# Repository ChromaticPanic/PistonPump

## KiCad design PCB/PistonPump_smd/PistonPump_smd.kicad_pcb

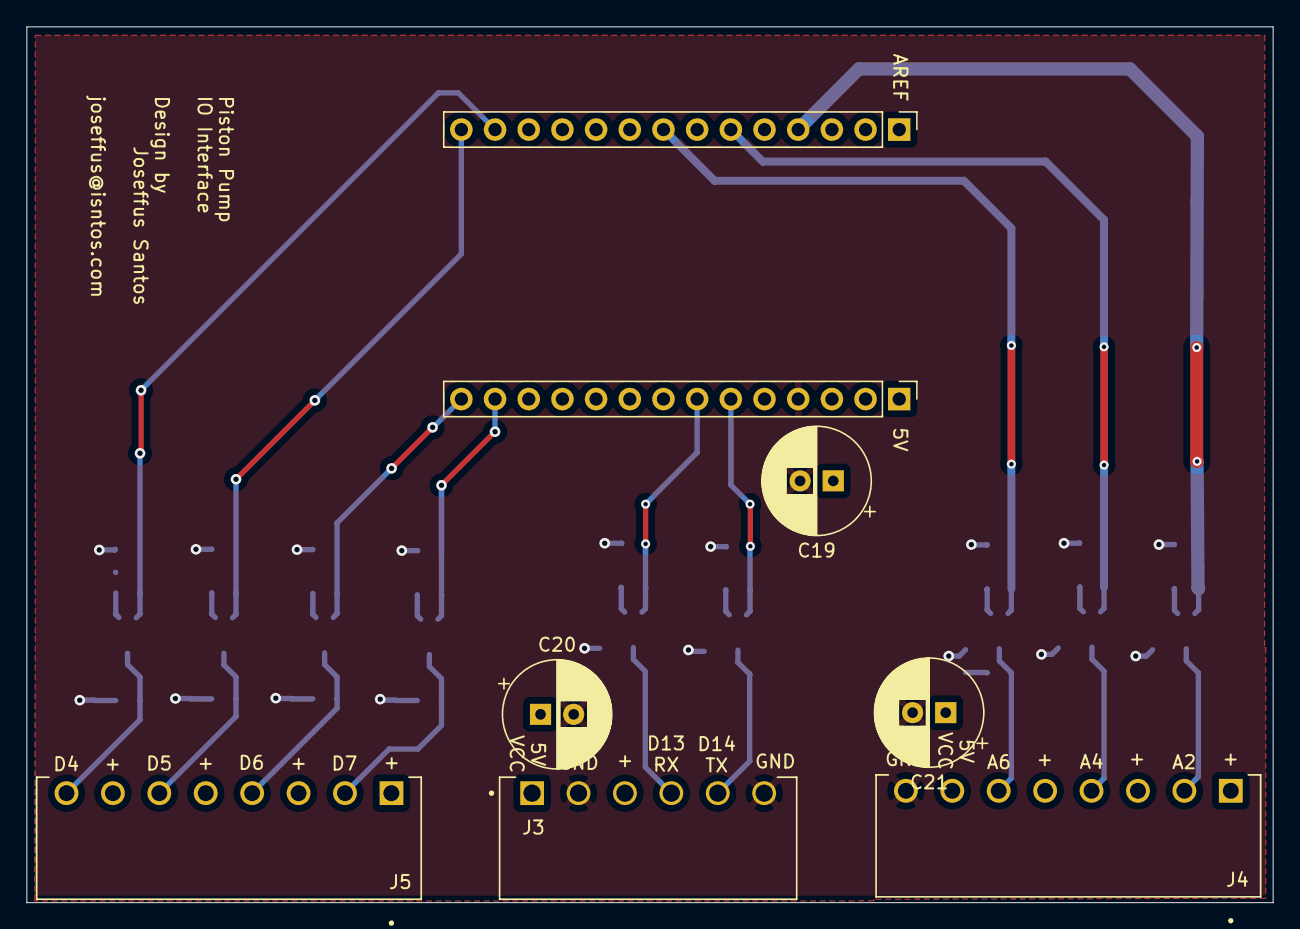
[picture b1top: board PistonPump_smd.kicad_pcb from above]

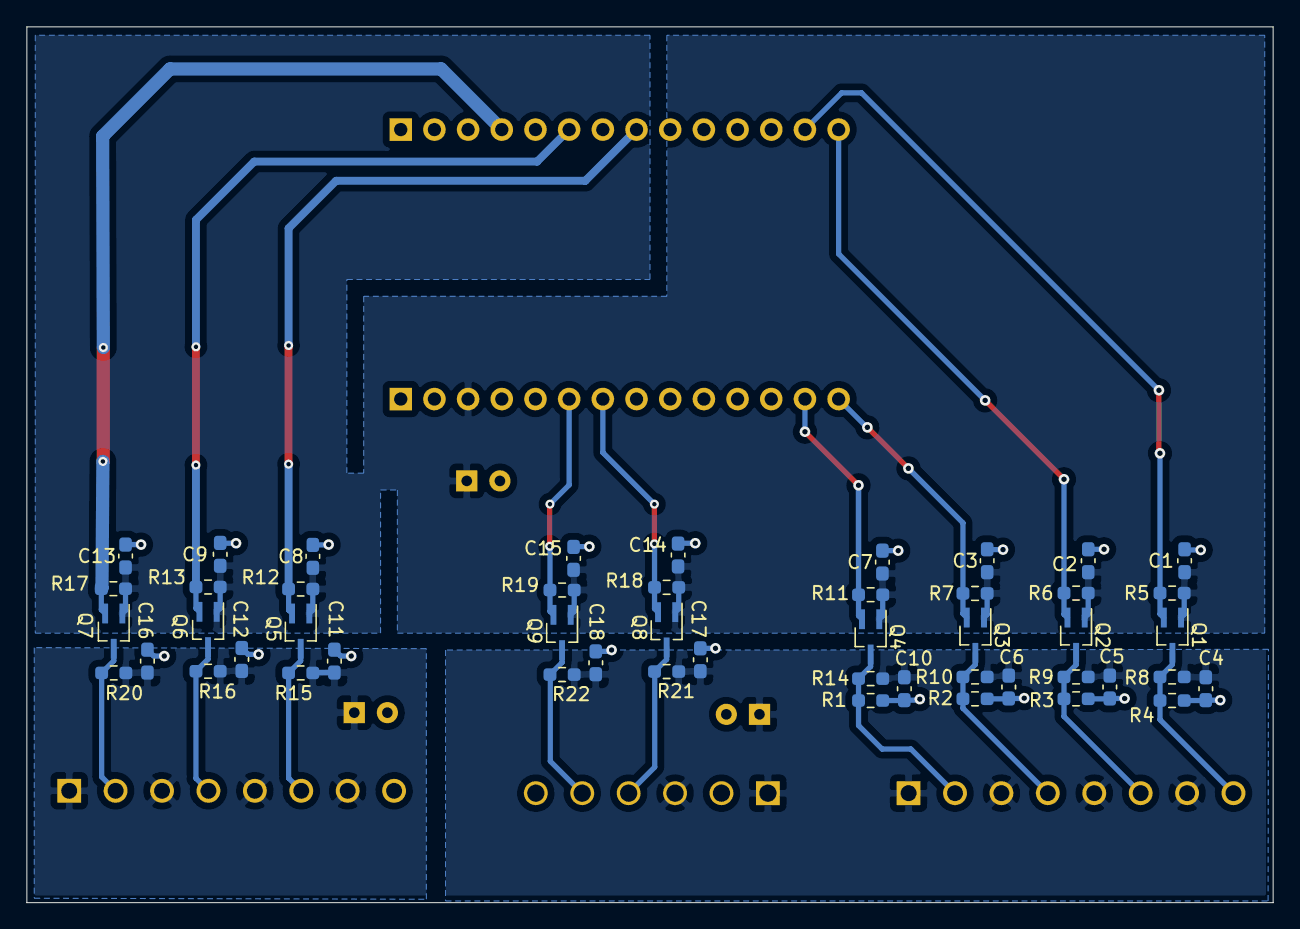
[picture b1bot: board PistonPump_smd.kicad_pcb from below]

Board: 2 copper layers, 94.0 x 66.0 mm, 57 parts (49 on the bottom side), 22 nets.

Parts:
C1, C2, C3, C4, C5, C6, C7, C8, C9, C10, C11, C12, C13, C14, C15, C16, C17, C18: 0.1uF; C_0603_1608Metric_Pad1.08x0.95mm_HandSolder
C19, C20, C21: 220uF; CP_Radial_D8.0mm_P2.50mm
J1, J2: Conn_01x14_Male; PinHeader_1x14_P2.54mm_Vertical
J3: Conn_01x06; MOLEX_0395021006
J4, J5: Conn_01x08; TE_284512-8
Q1, Q2, Q3, Q4, Q5, Q6, Q7, Q8, Q9: BSS138; SOT-323_SC-70_Handsoldering
R1, R2, R3, R4, R5, R6, R7, R8, R9, R10, R11, R12, R13, R14, R15, R16, R17, R18, R19, R20, R21, R22: 10k; R_0603_1608Metric_Pad0.98x0.95mm_HandSolder

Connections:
+3V3: C1.1, C2.1, C3.1, C7.1, C8.1, C9.1, C13.1, C14.1, C15.1, C19.1, J2.3, Q1.1, Q2.1, Q3.1, Q4.1, Q5.1, Q6.1, Q7.1, Q8.1, Q9.1, R5.1, R6.1, R7.1, R11.1, R12.1, R13.1, R17.1, R18.1, R19.1
+5V: C11.1, C12.1, C16.1, C21.1, J4.1, J4.3, J4.5, J4.7, R15.1, R16.1, R20.1
+5VD: C4.1, C5.1, C6.1, C10.1, C17.1, C18.1, C20.1, J3.1, J3.3, J5.1, J5.3, J5.5, J5.7, R8.1, R9.1, R10.1, R14.1, R21.1, R22.1
GND: C1.2, C2.2, C3.2, C4.2, C5.2, C6.2, C7.2, C8.2, C9.2, C10.2, C11.2, C12.2, C13.2, C14.2, C15.2, C16.2, C17.2, C18.2, C19.2, C20.2, C21.2, J2.4, J3.2, J3.6, J4.8, R1.1, R2.1, R3.1, R4.1
HV1: J5.8, Q1.3, R4.2, R8.2
HV2: J5.6, Q2.3, R3.2, R9.2
HV3: J5.4, Q3.3, R2.2, R10.2
HV4: J5.2, Q4.3, R1.2, R14.2
HV5: J4.6, Q5.3, R15.2
HV6: J4.4, Q6.3, R16.2
HV7: J4.2, Q7.3, R20.2
HV8: J3.4, Q8.3, R21.2
HV9: J3.5, Q9.3, R22.2
LV1: J1.13, Q1.2, R5.2
LV2: J1.14, Q2.2, R6.2
LV3: J2.14, Q3.2, R7.2
LV4: J2.13, Q4.2, R11.2
LV5: J1.8, Q5.2, R12.2
LV6: J1.6, Q6.2, R13.2
LV7: J1.4, Q7.2, R17.2
LV8: J2.7, Q8.2, R18.2
LV9: J2.6, Q9.2, R19.2

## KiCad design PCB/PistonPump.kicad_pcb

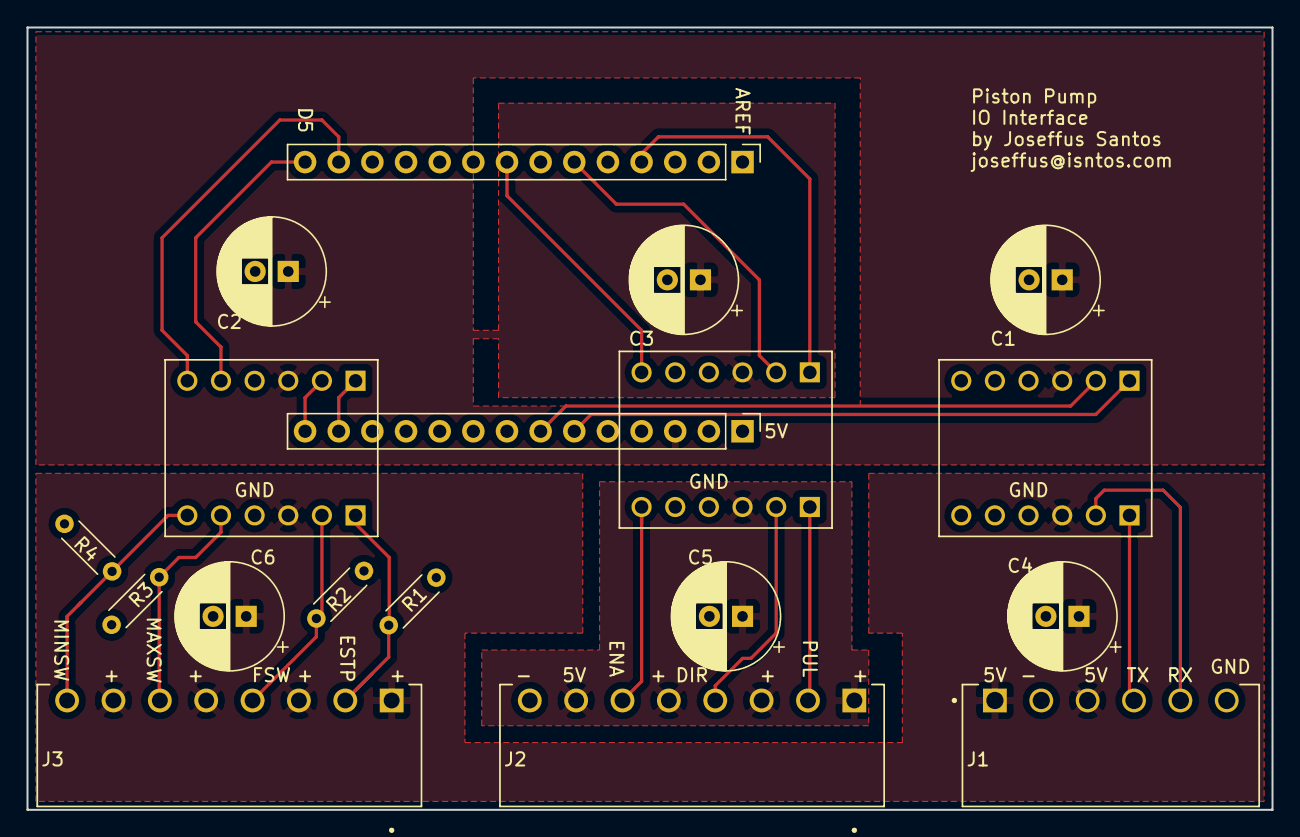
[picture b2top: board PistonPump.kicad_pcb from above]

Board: 2 copper layers, 94.0 x 59.1 mm, 18 parts (0 on the bottom side), 22 nets.

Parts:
C1, C2, C3, C4, C5, C6: CP; CP_Radial_D8.0mm_P2.50mm
J1: Conn_01x06; MOLEX_0395021006
J2, J3: Conn_01x08; TE_284512-8
J4, J5: Conn_01x14_Male; PinHeader_1x14_P2.54mm_Vertical
R1, R2, R3, R4: R_US; R_Axial_DIN0204_L3.6mm_D1.6mm_P5.08mm_Horizontal
U2, U3, U4: BOB-12009; CONV_BOB-12009

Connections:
+5V: C5.1, J2.1, J2.3, J2.5, J2.7, U3.HV
+5VD: C4.1, C6.1, J1.1, J1.3, J3.1, J3.3, J3.5, J3.7, U2.HV, U4.HV
/3V3: C1.1, C2.1, C3.1, J5.3, U2.LV, U3.LV, U4.LV
GND: C1.2, C2.2, C3.2, C4.2, C5.2, C6.2, J1.2, J1.6, J2.8, J5.4, R1.1, R2.1, R3.1, R4.1, U2.GND_1, U2.GND_2, U3.GND_1, U3.GND_2, U4.GND_1, U4.GND_2
unnamed: J1.4, U2.HV1
unnamed: J1.5, U2.HV2
unnamed: J2.2, U3.HV1
unnamed: J2.4, U3.HV2
unnamed: J2.6, U3.HV4
unnamed: J3.2, R1.2, U4.HV1
unnamed: J3.4, R2.2, U4.HV2
unnamed: J3.6, R3.2, U4.HV3
unnamed: J3.8, R4.2, U4.HV4
unnamed: J4.4, U3.LV1
unnamed: J4.6, U3.LV2
unnamed: J4.8, U3.LV4
unnamed: J4.13, U4.LV4
unnamed: J4.14, U4.LV3
unnamed: J5.6, U2.LV1
unnamed: J5.7, U2.LV2
unnamed: J5.13, U4.LV1
unnamed: J5.14, U4.LV2

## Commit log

2021-06-18 Reorg
2021-06-18 CAD files added
2021-06-18 switch to forward declarations
2021-06-18 constants
2021-06-19 improved modularization of functions
2021-06-19 all functions modular forward declared
2021-06-21 build_2021_06_20
2021-06-21 stable
2021-06-21 rename
2021-06-21 build before refactor
2021-06-21 Before SD refactor
2021-06-21 todo settings validation
2021-06-24 compiles
2021-07-22 refactored constants to define added debounce to zero, dispense functions
2021-08-04 production 2021-08-04
2021-08-12 main line 651
2021-08-13 block fsw while dispense fisx dispense algo inc def accel to 20
2021-08-13 Fixed min max push pull accel time
2021-08-13 added dispense blocking to mv to zero mv to max increased max dispense speed allowed
2021-08-26 Added Require zero at power cycle or any error
2021-08-26 pins
2021-12-23 current
2022-07-18 Limit switches will only be enabled when zeroing or moving to max
2022-07-18 FSW software debounce 100ms Prevent dispensing if not zeroed Estop press will require zeroing after
2022-07-18 Fixed string const to char* compile warning
2022-07-18 Fixed fsw debounce function
2022-09-06 Refactor Step Pulse
    Stepper pulsing refactored
    Added acceleration
    Updated SD read method
2022-09-06 Bi directional accel
    Added acceleration in both directions when dispensing
2022-09-06 increased delay after enable
2022-09-06 inverted guard statement logic
